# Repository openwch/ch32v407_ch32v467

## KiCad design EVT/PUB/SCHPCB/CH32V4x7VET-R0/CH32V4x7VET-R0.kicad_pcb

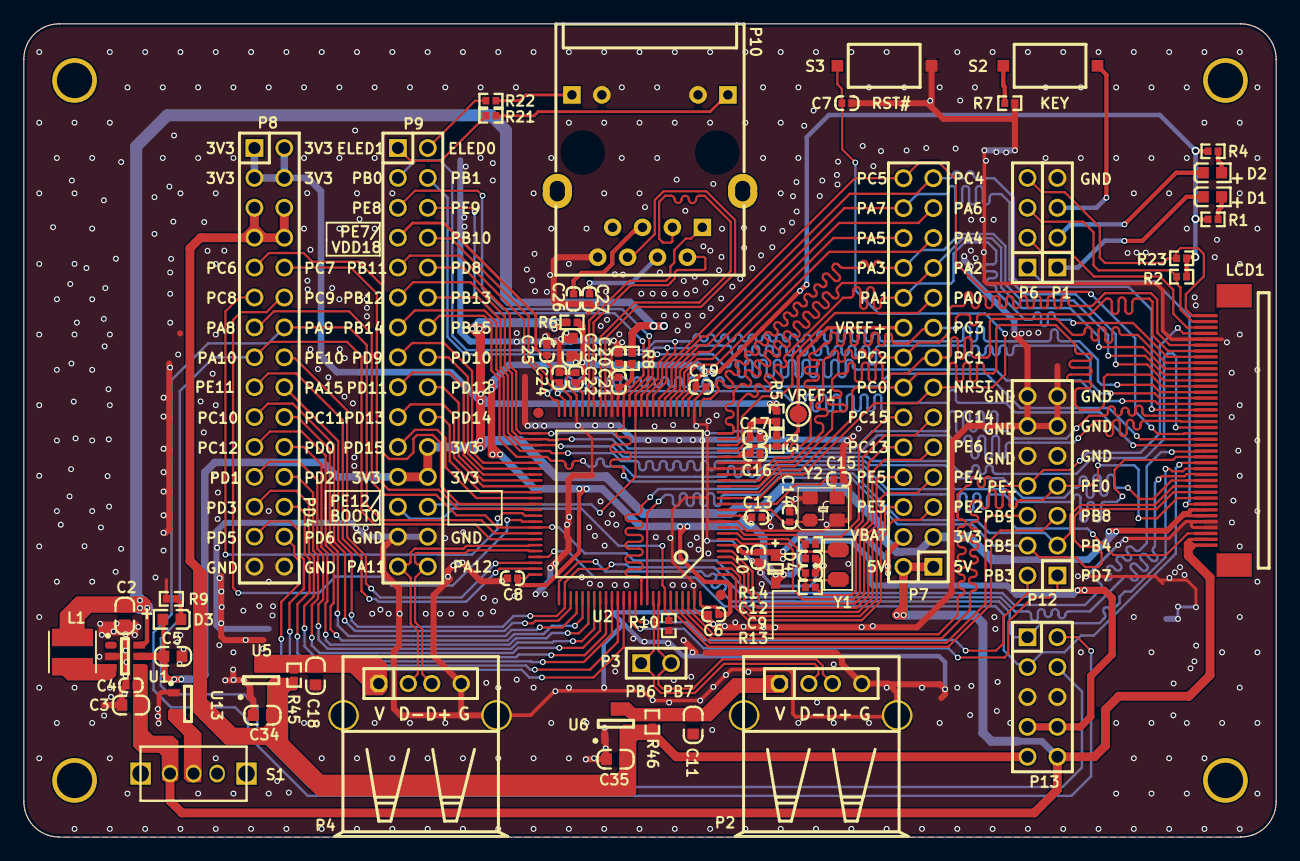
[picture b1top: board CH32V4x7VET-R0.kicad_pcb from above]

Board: 2 copper layers, 106.4 x 69.1 mm, 73 parts (0 on the bottom side), 117 nets.

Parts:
C2: NC(10uF); 0603_C
C3, C5, C11, C18, C23, C34, C35: 10uF; 0603_C
C4: 1uF; 0402_C
C6, C8, C10, C13, C16, C17, C19, C21, C22, C24, C26, C27: 0.1uF; 0402_C
C7: 22nF; 0402_C
C9, C12: 12pF; 0402_C
C14, C15: 18pF; 0402_C
C20, C25: 2.2uF; 0402_C
D1: BLUE; 0603+
D2, D3: RED; 0603+
D4: B0520WS; SOD-323
L1: NC(2.2uH); CD32
LCD1: NC(MY-RGB); FPC40P-0.5-FK750M3
P1: HEADER 4; SIP4-2.54mm
P2: USBHS2; USBAF
P3: HEADER 2; SIP2-2.54mm
P4: USBHS1; USBAF
P6: NC(HEADER 4); SIP4-2.54mm
P7: HEADER 14x2; IDC28-2.54MM
P8, P9: HEADER 15x2; IDC30-2.54MM
P10: HR911105A
P12: HEADER 7x2; IDC14-2.54mm
P13: LINK; IDC10-2.54mm
R1, R4, R9: 1K; 0402
R2, R23: NC(4.7K); 0402
R3, R5, R6: 0R; 0402
R7, R10: 10K; 0402
R8, R13, R14: NC(0R); 0402
R21, R22: 470; 0402
R45, R46: NC(0Ω); 0402
S1: SW SPDT; SW1
S2: KEY; SMD_6.1x3.65x2.5mm-KEY
S3: RST#; SMD_6.1x3.65x2.5mm-KEY
U1: CH2003V; SOT-23-6
U2: CH32V467VET; LQFP100
U5, U6, U13: CH213; SOT-23-3
VREF1: PAD; TESTPOINT1
Y1: 32768Hz; FC-135
Y2: 25MHz; XT3225

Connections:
1V2: C2.2, L1.2, R8.2, U1.6
3V3: C5.2, D3.1, LCD1.6, LCD1.7, P7.3, P8.1, P8.2, P8.3, P8.4, P9.22, P9.23, P9.24, R5.1, R6.1, U1.5
+5V: C3.2, C4.2, LCD1.1, LCD1.2, P7.1, P7.2, P13.10, S1.2, U1.4
BOOT0: P9.25, R10.2, U2.94
BOOT1: LCD1.25, P9.26, U2.37
ELED0: P9.2, R22.1
ELED1: P9.1, R21.1
GND: C2.1, C3.1, C4.1, C5.1, C6.1, C7.1, C8.2, C9.1, C10.1, C11.2, C12.1, C13.2, C14.1, C15.1, C16.2, C17.2, C18.2, C19.1, C20.1, C21.1, C22.1, C23.1, C24.1, C25.1, C26.1, C27.1, C34.2, C35.2, LCD1.4, LCD1.5, LCD1.36, P1.4, P2.0, P2.4, P4.0, P4.4, P8.29, P8.30, P9.27, P9.28, P10.8, P10.10, P10.11, P12.9, P12.10, P12.11, P12.12, P12.13, P12.14, P13.5, P13.6, R7.1, R9.2, R10.1, S3.1, U1.2, U2.10, U2.19, U2.20, U2.27, U2.41, U2.47, U2.99, U5.1, U6.1, U13.1, Y2.2, Y2.4
KEY: P1.3, S2.1
LED1: D1.2, P1.1
LED2: D2.2, P1.2
MDIRN: P10.6, U2.42
MDIRP: P10.3, U2.43
MDITN: P10.2, U2.44
MDITP: P10.1, U2.45
NRST: C7.2, P7.13, S3.2, U2.14
NetC26_2: C26.2, P10.5
NetC27_2: C27.2, P10.4
NetD1_1: D1.1, R1.2
NetD2_1: D2.1, R4.2
NetD3_2: D3.2, R9.1
NetL1_1: L1.1, U1.3
NetP10_9: P10.9, R21.2
NetP10_12: P10.12, R22.2
NetR7_2: R7.2, S2.2
NetS1_1: S1.1, U13.2
PA0: P7.19, U2.23
PA1: LCD1.33, P7.20, U2.24
PA2: LCD1.31, P7.21, U2.25
PA3: LCD1.30, P7.22, U2.26
PA4: P7.23, U2.29
PA5: P7.24, U2.30
PA6: P7.25, U2.31
PA7: LCD1.29, P7.26, U2.32
PA8: LCD1.17, P8.13, U2.67
PA9: P8.14, P13.2, U2.68
PA10: P8.15, P13.4, U2.69
PA11: P4.2, P9.29, U2.70
PA12: P4.3, P9.30, U2.71
PA13: LCD1.15, P13.3, U2.72
PA14: LCD1.14, P13.1, U2.76
PA15: LCD1.13, P8.18, U2.77
PB0: LCD1.27, P9.3, U2.35
PB1: LCD1.26, P9.4, U2.36
PB3: P12.2, U2.89
PB4: LCD1.11, P12.3, U2.90
PB5: LCD1.10, P12.4, U2.91
PB6: P2.2, P3.1, U2.92
PB7: P2.3, P3.2, U2.93
PB8: P12.5, U2.95
PB9: P12.6, U2.96
PB10: LCD1.18, P9.8, U2.49
PB11: LCD1.19, P9.9, U2.50
PB12: LCD1.22, P9.11, U2.52
PB13: LCD1.21, P9.12, U2.53
PB14: LCD1.12, P9.13, U2.54
PB15: LCD1.16, P9.14, U2.55
PC0: LCD1.28, P7.14, U2.15
PC1: LCD1.32, P7.15, U2.16
PC2: LCD1.35, P7.16, U2.17
PC3: LCD1.34, P7.17, U2.18
PC4: LCD1.24, P7.27, U2.33
PC5: LCD1.20, P7.28, U2.34
PC6: P8.9, U2.63
PC7: P8.10, U2.64
PC8: P8.11, U2.65
PC9: P8.12, U2.66
PC10: P8.19, U2.78
PC11: P8.20, U2.79
PC12: P8.21, U2.80
PC13: P7.10, U2.7
PC14: P7.11, R13.1
PC15: P7.12, R14.1
PD0: P8.22, U2.81
PD1: P8.23, U2.82
PD2: P8.24, U2.83
PD3: P8.25, U2.84
PD4: P8.26, U2.85
PD5: P8.27, U2.86
PD6: P8.28, U2.87
PD7: P12.1, U2.88
PD8: LCD1.23, P9.10, U2.51
PD9: P9.15, U2.56
PD10: P9.16, U2.57
PD11: P9.17, U2.58
PD12: P9.18, U2.59
PD13: P9.19, U2.60
PD14: P9.20, U2.61
PD15: P9.21, U2.62
PE0: LCD1.9, P12.7, U2.97
PE1: LCD1.37, P12.8, U2.98
PE2: P7.5, U2.1
PE3: P7.6, U2.2
PE4: P7.7, U2.3
PE5: P7.8, U2.4
PE6: P7.9, U2.5
PE8: P9.5, U2.38
PE9: LCD1.3, P9.6, U2.39
PE10: P8.16, U2.73
PE11: P8.17, U2.74
TOUCH_INT: LCD1.38, P6.2
TOUCH_RST: LCD1.8, P6.1
TOUCH_SCLK: LCD1.39, P6.3, R2.2
TOUCH_SDA: LCD1.40, P6.4, R23.2
VBAT: C10.2, D4.1, P7.4, U2.6
VBUS: C34.1, C35.1, P8.5, P8.6, P8.7, P8.8, P13.9, R45.1, R46.1, U5.2, U6.2, U13.3
VBUS_P1: C18.1, P4.1, R45.2, U5.3
VBUS_P2: C11.1, P2.1, R46.2, U6.3
VDD: C6.2, C8.1, C13.1, C19.2, C22.2, C23.2, D4.2, P13.7, P13.8, R1.1, R2.1, R4.1, R6.2, R23.1, U2.11, U2.28, U2.46, U2.75, U2.100
VDD18: C24.2, C25.2, P9.7, U2.48
VDDA: C17.1, R3.1, R5.2, U2.22
VDDK: C20.2, C21.2, R8.1, U2.40
VREF+: C16.1, P7.18, R3.2, U2.21, VREF1.1
X32KI: C9.2, R13.2, U2.8, Y1.1
X32KO: C12.2, R14.2, U2.9, Y1.2
XI: C14.2, U2.12, Y2.1
XO: C15.2, U2.13, Y2.3

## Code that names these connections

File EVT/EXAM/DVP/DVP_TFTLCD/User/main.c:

/********************************** (C) COPYRIGHT *******************************
* File Name          : main.c
* Author             : WCH
* Version            : V1.0.1
* Date               : 2026/10/14
* Description        : Main program body.
*********************************************************************************
* Copyright (c) 2021 Nanjing Qinheng Microelectronics Co., Ltd.
* Attention: This software (modified or not) and binary are used for 
* microcontroller manufactured by Nanjing Qinheng Microelectronics.
*******************************************************************************/
#include "debug.h"
#include "lcd.h"
#include "ov5640.h"
#include "ov2640.h"
/*
 *@Note
  DVP routine to operate ov2640\ov5640 camera video mode to display image on TFTLCD:
  DVP--PIN:
    D10--PD6
    D11--PD2
    D8--PC10
    D9--PC12
    DPWDN--PE5
    DPCLK--PA6
    D7--PB9
    D6--PB8
    D5--PB6
    D4--PC11
    D3--PC9
    D2--PC8
    D1--PA10
    D0--PA9
    RESET--PE4
    SCL--PE2
    SDA--PE3
    HSYNC--PA4
    VSYNC--PA5
  FSMC routine to operate TFTLCD-LCD--PIN:
    PD7--NE1(CS)
    PD12--RS
    PD5 --FSMC_NEW(WR)
    PD4 --FSMC_NOE(RD)
    PA15 --LCDRST#
    PD14--FSMC_D0
    PD15--FSMC_D1
    PD0 --FSMC_D2
    PD1--FSMC_D3
    PE7--FSMC_D4
    PE8 --FSMC_D5
    PE9 --FSMC_D6
    PE10--FSMC_D7
    PE11--FSMC_D8
    PB11--FSMC_D9
    PB12--FSMC_D10
    PB13--FSMC_D11
    PB14--FSMC_D12
    PD8 --FSMC_D13
    PD9 --FSMC_D14
    PD10--FSMC_D15
    PB1--BL
 */

/* Camera module selection */
#define OV2640_Module  0
#define OV5640_Module  1
#define CAMERA_SELECT  OV5640_Module

#if(CAMERA_SELECT == OV2640_Module)
uint16_t ImageDataOv2640[2 * OV2640_RGB565_WIDTH] = {0};
#elif(CAMERA_SELECT == OV5640_Module)
uint16_t ImageDataOv5640[2 * OV5640_RGB565_WIDTH] = {0};
#endif

volatile UINT32 frame_cnt = 0;
volatile UINT32 href_cnt = 0;

void DVP_IRQHandler(void) __attribute__ ((interrupt ("WCH-Interrupt-fast")));

/*********************************************************************
 * @fn      DMA_SRAMLCD_Enable
 *
 * @brief   Enable SRAMLCD DMA transmission
 *
 * @return  none
 */
void DMA_SRAMLCD_Enable(void)
{
    DMA_Cmd(DMA2_Channel5, DISABLE );
    DMA_SetCurrDataCounter(DMA2_Channel5,lcddev.width);
    DMA_Cmd(DMA2_Channel5, ENABLE);
}

/*********************************************************************
 * @fn      LCD_Reset_GPIO_Init
 *
 * @brief   Init LCD reset GPIO.
 *
 * @return  none
 */
void LCD_Reset_GPIO_Init(void)
{
    GPIO_InitTypeDef  GPIO_InitStructure={0};

    RCC_PB2PeriphClockCmd(RCC_PB2Periph_GPIOA, ENABLE);

    GPIO_InitStructure.GPIO_Pin = GPIO_Pin_15;
    GPIO_InitStructure.GPIO_Mode = GPIO_Mode_Out_PP;
    GPIO_InitStructure.GPIO_Speed = GPIO_Speed_High;
    GPIO_Init(GPIOA, &GPIO_InitStructure);
    GPIO_SetBits(GPIOA,GPIO_Pin_15);
}

/*********************************************************************
 * @fn      DMA_SRAMLCD_Init
 *
 * @brief   Init SRAMLCD DMA
 *
 * @param   ddr: DVP data memory base addr.
 *
 * @return  none
 */
void DMA_SRAMLCD_Init(u32 ddr)
{
    DMA_InitTypeDef DMA_InitStructure={0};

    RCC_HBPeriphClockCmd(RCC_HBPeriph_DMA2, ENABLE);

    DMA_DeInit(DMA2_Channel5);

    DMA_InitStructure.DMA_PeripheralBaseAddr = ddr;
    DMA_InitStructure.DMA_MemoryBaseAddr = (u32)&LCD->LCD_RAM;
    DMA_InitStructure.DMA_DIR = DMA_DIR_PeripheralSRC;
    DMA_InitStructure.DMA_BufferSize = 0;
    DMA_InitStructure.DMA_PeripheralInc = DMA_PeripheralInc_Enable;
    DMA_InitStructure.DMA_MemoryInc = DMA_MemoryInc_Disable;
    DMA_InitStructure.DMA_PeripheralDataSize = DMA_PeripheralDataSize_HalfWord;
    DMA_InitStructure.DMA_MemoryDataSize = DMA_MemoryDataSize_HalfWord;
    DMA_InitStructure.DMA_Mode = DMA_Mode_Normal;
    DMA_InitStructure.DMA_Priority = DMA_Priority_Medium;
    DMA_InitStructure.DMA_M2M = DMA_M2M_Enable;
    DMA_Init(DMA2_Channel5, &DMA_InitStructure);
}

/*********************************************************************
 * @fn      DVP_Function_Init
 *
 * @brief   Init DVP
 *
 * @return  none
 */
void DVP_Function_Init(void) 
{
    DVP_InitTypeDef DVP_InitStructure = {0};
    RCC_HBPeriphClockCmd(RCC_HBPeriph_DVP, ENABLE);

    DVP_DeInit();
    DVP_InitStructure.DVP_DataSize = DVP_DataSize_8b;
#if(CAMERA_SELECT == OV2640_Module)
    DVP_InitStructure.DVP_COL_NUM = OV2640_RGB565_WIDTH * 2;
    DVP_InitStructure.DVP_ROW_NUM = OV2640_RGB565_HEIGHT;
#elif(CAMERA_SELECT == OV5640_Module)
    DVP_InitStructure.DVP_COL_NUM = OV5640_RGB565_WIDTH * 2;
    DVP_InitStructure.DVP_ROW_NUM = OV5640_RGB565_HEIGHT;
#endif
    DVP_InitStructure.DVP_HCLK_P = DVP_Hclk_P_Rising;
    DVP_InitStructure.DVP_HSYNC_P = DVP_Hsync_P_High;
    DVP_InitStructure.DVP_VSYNC_P = DVP_Vsync_P_High;
#if(CAMERA_SELECT == OV2640_Module)
    DVP_InitStructure.DVP_DMA_BUF0_Addr = (uint32_t)(ImageDataOv2640);
    DVP_InitStructure.DVP_DMA_BUF1_Addr = (uint32_t)(ImageDataOv2640 + OV2640_RGB565_WIDTH);
#elif(CAMERA_SELECT == OV5640_Module)
    DVP_InitStructure.DVP_DMA_BUF0_Addr = (uint32_t)(ImageDataOv5640);
    DVP_InitStructure.DVP_DMA_BUF1_Addr = (uint32_t)(ImageDataOv5640 + OV5640_RGB565_WIDTH);
#endif
    DVP_InitStructure.DVP_FrameCapRate = DVP_FrameCapRate_100P;
    DVP_InitStructure.DVP_JPEGMode = DISABLE;
    DVP_InitStructure.DVP_CaptureMode = DVP_CaptureMode_Continuous;
    DVP_Init(&DVP_InitStructure);

    DVP_ReceiveCircuitResetCmd(DISABLE);
    DVP_FIFO_ResetCmd(DISABLE);

    NVIC_EnableIRQ(DVP_IRQn);
    NVIC_SetPriority(DVP_IRQn, 0);

    DVP_ITConfig(DVP_IT_STR_FRM | DVP_IT_ROW_DONE | DVP_IT_FRM_DONE | DVP_IT_FIFO_OV | DVP_IT_STP_FRM, ENABLE);

    DVP_DMACmd(ENABLE);
    DVP_Cmd(ENABLE);
}

/*********************************************************************
 * @fn      DVP_IRQHandler
 *
 * @brief   This function handles DVP exception.
 *
 * @return  none
 */
void DVP_IRQHandler(void)
{
    if(DVP_GetITStatus(DVP_IT_ROW_DONE) != RESET)
    {
        DVP_ClearITPendingBit(DVP_IT_ROW_DONE);

        if(href_cnt % 2)
        {
            /* Send DVP data to LCD */
            DMA_Cmd(DMA2_Channel5, DISABLE);    
#if(CAMERA_SELECT == OV2640_Module)
            DMA_SetCurrDataCounter(DMA2_Channel5, OV2640_RGB565_WIDTH * 2);
            DMA2_Channel5->PADDR = (uint32_t)(ImageDataOv2640);
#elif(CAMERA_SELECT == OV5640_Module)
            DMA_SetCurrDataCounter(DMA2_Channel5, OV5640_RGB565_WIDTH * 2);
            DMA2_Channel5->PADDR = (uint32_t)(ImageDataOv5640);
#endif     
            DMA_Cmd(DMA2_Channel5, ENABLE);
        }
        href_cnt++;
    }

    if(DVP_GetITStatus(DVP_IT_FRM_DONE) != RESET)
    {
        DVP_ClearITPendingBit(DVP_IT_FRM_DONE);
        href_cnt = 0;
    }

    if(DVP_GetITStatus(DVP_IT_STR_FRM) != RESET)
    {
        DVP_ClearITPendingBit(DVP_IT_STR_FRM);
        frame_cnt++;
    }

    if(DVP_GetITStatus(DVP_IT_STP_FRM) != RESET)
    {
        DVP_ClearITPendingBit(DVP_IT_STP_FRM);
    }

    if(DVP_GetITStatus(DVP_IT_FIFO_OV) != RESET)
    {
        DVP_ClearITPendingBit(DVP_IT_FIFO_OV);
    }
}

/*********************************************************************
 * @fn      main
 *
 * @brief   Main program.
 *
 * @return  none
 */
int main(void)
{
	SystemCoreClockUpdate();
	Delay_Init();
	USART_Printf_Init(115200);	
	printf("SystemClk:%u\r\n",SystemCoreClock);
	printf( "ChipID:%08x\r\n", DBGMCU_GetCHIPID() );

#if(CAMERA_SELECT == OV2640_Module)
    LCD_Reset_GPIO_Init();
    LCD_Init();   
   while(OV2640_Init())
    {
        printf("Camera Initialize failed.\r\n");
        Delay_Ms(1000);
    }
    printf("Camera Initialize Success.\r\n");

    Delay_Ms(1000);

    OV2640_RGB565_Mode_Init();
    Delay_Ms(1000);   

    printf("RGB565 Mode...\r\n");

    DMA_SRAMLCD_Init((u32)ImageDataOv2640);
    DVP_Function_Init();
#endif

#if(CAMERA_SELECT == OV5640_Module)
    uint8_t tempstr[50]; 
    LCD_Reset_GPIO_Init();
    LCD_Init();   
    LCD_Display_Dir(1);
    
    sprintf ((char*)tempstr,"height: %d  width: %d  id: %#x\n", lcddev.height, lcddev.width, lcddev.id);
    LCD_ShowString(0,120-12,320,48,16,tempstr);

    LCD_SetCursor (0, 0);
    LCD_WriteRAM_Prepare();

    while(OV5640_Init()) {
        printf("Camera Initialize failed.\r\n");
        Delay_Ms(1000);
    }
    printf("Camera Initialize Success.\r\n");

    OV5640_RGB565_Mode_Init();
    Delay_Ms(500);
    printf("RGB565 Mode...\r\n");
    DMA_SRAMLCD_Init((uint32_t)ImageDataOv5640);
    DVP_Function_Init();
#endif

    while(1);
}

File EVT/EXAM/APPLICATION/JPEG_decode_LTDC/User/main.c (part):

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    RCC_PB2PeriphClockCmd(RCC_PB2Periph_GPIOE, ENABLE);
    GPIO_PinRemapConfig(GPIO_Remap_SWJ_Disable, ENABLE);

    // LTDC_CLK PE1
    GPIO_InitStructure.GPIO_Pin   = GPIO_Pin_1;
    GPIO_InitStructure.GPIO_Speed = GPIO_Speed_High;
    GPIO_InitStructure.GPIO_Mode  = GPIO_Mode_AF_PP;
    GPIO_Init(GPIOE, &GPIO_InitStructure);

    // LTDC_HSYNC PB4
    GPIO_InitStructure.GPIO_Pin   = GPIO_Pin_4;
    GPIO_InitStructure.GPIO_Speed = GPIO_Speed_High;
    GPIO_InitStructure.GPIO_Mode  = GPIO_Mode_AF_PP;
    GPIO_Init(GPIOB, &GPIO_InitStructure);

    // LTDC_VSYNC PB5
    GPIO_InitStructure.GPIO_Pin   = GPIO_Pin_5;
    GPIO_InitStructure.GPIO_Speed = GPIO_Speed_High;
    GPIO_InitStructure.GPIO_Mode  = GPIO_Mode_AF_PP;
    GPIO_Init(GPIOB, &GPIO_InitStructure);

    // LTDC_DE PE0
    GPIO_InitStructure.GPIO_Pin   = GPIO_Pin_0;
    GPIO_InitStructure.GPIO_Speed = GPIO_Speed_High;
    GPIO_InitStructure.GPIO_Mode  = GPIO_Mode_AF_PP;
    GPIO_Init(GPIOE, &GPIO_InitStructure);

    // LTDC_R0 PC0
    GPIO_InitStructure.GPIO_Pin   = GPIO_Pin_0;
    GPIO_InitStructure.GPIO_Speed = GPIO_Speed_High;
    GPIO_InitStructure.GPIO_Mode  = GPIO_Mode_AF_PP;
    GPIO_Init(GPIOC, &GPIO_InitStructure);

    // LTDC_R1 PC1
    GPIO_InitStructure.GPIO_Pin   = GPIO_Pin_1;
    GPIO_InitStructure.GPIO_Speed = GPIO_Speed_High;
    GPIO_InitStructure.GPIO_Mode  = GPIO_Mode_AF_PP;
    GPIO_Init(GPIOC, &GPIO_InitStructure);

    // LTDC_R2 PC2
    GPIO_InitStructure.GPIO_Pin   = GPIO_Pin_2;
    GPIO_InitStructure.GPIO_Speed = GPIO_Speed_High;
    GPIO_InitStructure.GPIO_Mode  = GPIO_Mode_AF_PP;
    GPIO_Init(GPIOC, &GPIO_InitStructure);

    // LTDC_R3 PC3
    GPIO_InitStructure.GPIO_Pin   = GPIO_Pin_3;
    GPIO_InitStructure.GPIO_Speed = GPIO_Speed_High;
    GPIO_InitStructure.GPIO_Mode  = GPIO_Mode_AF_PP;
    GPIO_Init(GPIOC, &GPIO_InitStructure);

    // LTDC_R4 PA1
    GPIO_InitStructure.GPIO_Pin   = GPIO_Pin_1;
    GPIO_InitStructure.GPIO_Speed = GPIO_Speed_High;
    GPIO_InitStructure.GPIO_Mode  = GPIO_Mode_AF_PP;
    GPIO_Init(GPIOA, &GPIO_InitStructure);

    // LTDC_R5 PA2
    GPIO_InitStructure.GPIO_Pin   = GPIO_Pin_2;
    GPIO_InitStructure.GPIO_Speed = GPIO_Speed_High;
    GPIO_InitStructure.GPIO_Mode  = GPIO_Mode_AF_PP;
    GPIO_Init(GPIOA, &GPIO_InitStructure);

    // LTDC_R6 PA3
    GPIO_InitStructure.GPIO_Pin   = GPIO_Pin_3;
    GPIO_InitStructure.GPIO_Speed = GPIO_Speed_High;
    GPIO_InitStructure.GPIO_Mode  = GPIO_Mode_AF_PP;
    GPIO_Init(GPIOA, &GPIO_InitStructure);

    // LTDC_R7 PA7
    GPIO_InitStructure.GPIO_Pin   = GPIO_Pin_7;
    GPIO_InitStructure.GPIO_Speed = GPIO_Speed_High;
    GPIO_InitStructure.GPIO_Mode  = GPIO_Mode_AF_PP;
    GPIO_Init(GPIOA, &GPIO_InitStructure);

    // LTDC_G0 PC4
    GPIO_InitStructure.GPIO_Pin   = GPIO_Pin_4;
    GPIO_InitStructure.GPIO_Speed = GPIO_Speed_High;
    GPIO_InitStructure.GPIO_Mode  = GPIO_Mode_AF_PP;
    GPIO_Init(GPIOC, &GPIO_InitStructure);

    // LTDC_G1 PC5
    GPIO_InitStructure.GPIO_Pin   = GPIO_Pin_5;
    GPIO_InitStructure.GPIO_Speed = GPIO_Speed_High;
    GPIO_InitStructure.GPIO_Mode  = GPIO_Mode_AF_PP;
    GPIO_Init(GPIOC, &GPIO_InitStructure);

    // LTDC_G2 PB0
    GPIO_InitStructure.GPIO_Pin   = GPIO_Pin_0;
    GPIO_InitStructure.GPIO_Speed = GPIO_Speed_High;
    GPIO_InitStructure.GPIO_Mode  = GPIO_Mode_AF_PP;
    GPIO_Init(GPIOB, &GPIO_InitStructure);

    // LTDC_G3 PB1
    GPIO_InitStructure.GPIO_Pin   = GPIO_Pin_1;
    GPIO_InitStructure.GPIO_Speed = GPIO_Speed_High;
    GPIO_InitStructure.GPIO_Mode  = GPIO_Mode_AF_PP;
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    GPIO_InitStructure.GPIO_Mode  = GPIO_Mode_AF_PP;
    GPIO_Init(GPIOB, &GPIO_InitStructure);

    // LTDC_G5 PD8
    GPIO_InitStructure.GPIO_Pin   = GPIO_Pin_8;
    GPIO_InitStructure.GPIO_Speed = GPIO_Speed_High;
    GPIO_InitStructure.GPIO_Mode  = GPIO_Mode_AF_PP;
    GPIO_Init(GPIOD, &GPIO_InitStructure);

    // LTDC_G6 PB12
    GPIO_InitStructure.GPIO_Pin   = GPIO_Pin_12;
    GPIO_InitStructure.GPIO_Speed = GPIO_Speed_High;
    GPIO_InitStructure.GPIO_Mode  = GPIO_Mode_AF_PP;
    GPIO_Init(GPIOB, &GPIO_InitStructure);

    // LTDC_G7 PB13
    GPIO_InitStructure.GPIO_Pin   = GPIO_Pin_13;
    GPIO_InitStructure.GPIO_Speed = GPIO_Speed_High;
    GPIO_InitStructure.GPIO_Mode  = GPIO_Mode_AF_PP;
    GPIO_Init(GPIOB, &GPIO_InitStructure);

    // LTDC_B0 PB14
    GPIO_InitStructure.GPIO_Pin   = GPIO_Pin_14;
    GPIO_InitStructure.GPIO_Speed = GPIO_Speed_High;
    GPIO_InitStructure.GPIO_Mode  = GPIO_Mode_AF_PP;
    GPIO_Init(GPIOB, &GPIO_InitStructure);

    // LTDC_B1 PB15
    GPIO_InitStructure.GPIO_Pin   = GPIO_Pin_15;
    GPIO_InitStructure.GPIO_Speed = GPIO_Speed_High;
    GPIO_InitStructure.GPIO_Mode  = GPIO_Mode_AF_PP;
    GPIO_Init(GPIOB, &GPIO_InitStructure);

    // LTDC_B2 PB11
    GPIO_InitStructure.GPIO_Pin   = GPIO_Pin_11;
    GPIO_InitStructure.GPIO_Speed = GPIO_Speed_High;
    GPIO_InitStructure.GPIO_Mode  = GPIO_Mode_AF_PP;
    GPIO_Init(GPIOB, &GPIO_InitStructure);

    // LTDC_B3 PB10
    GPIO_InitStructure.GPIO_Pin   = GPIO_Pin_10;
    GPIO_InitStructure.GPIO_Speed = GPIO_Speed_High;
    GPIO_InitStructure.GPIO_Mode  = GPIO_Mode_AF_PP;
    GPIO_Init(GPIOB, &GPIO_InitStructure);

    // LTDC_B4 PA8
    GPIO_InitStructure.GPIO_Pin   = GPIO_Pin_8;
    GPIO_InitStructure.GPIO_Speed = GPIO_Speed_High;
    GPIO_InitStructure.GPIO_Mode  = GPIO_Mode_AF_PP;
    GPIO_Init(GPIOA, &GPIO_InitStructure);

    // LTDC_B5 PA13
    GPIO_InitStructure.GPIO_Pin   = GPIO_Pin_13;
    GPIO_InitStructure.GPIO_Speed = GPIO_Speed_High;
    GPIO_InitStructure.GPIO_Mode  = GPIO_Mode_AF_PP;
    GPIO_Init(GPIOA, &GPIO_InitStructure);

    // LTDC_B6 PA14
    GPIO_InitStructure.GPIO_Pin   = GPIO_Pin_14;
    GPIO_InitStructure.GPIO_Speed = GPIO_Speed_High;
    GPIO_InitStructure.GPIO_Mode  = GPIO_Mode_AF_PP;
    GPIO_Init(GPIOA, &GPIO_InitStructure);

    // LTDC_B7 PA15
    GPIO_InitStructure.GPIO_Pin   = GPIO_Pin_15;
    GPIO_InitStructure.GPIO_Speed = GPIO_Speed_High;
    GPIO_InitStructure.GPIO_Mode  = GPIO_Mode_AF_PP;
    GPIO_Init(GPIOA, &GPIO_InitStructure);

    // 背光灯使能 PE9
    GPIO_InitStructure.GPIO_Pin   = GPIO_Pin_9;
    GPIO_InitStructure.GPIO_Speed = GPIO_Speed_High;
    GPIO_InitStructure.GPIO_Mode  = GPIO_Mode_Out_PP;
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
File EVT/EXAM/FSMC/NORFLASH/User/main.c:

/********************************** (C) COPYRIGHT *******************************
* File Name          : main.c
* Author             : WCH
* Version            : V1.0.0
* Date               : 2026/10/14
* Description        : Main program body.
*********************************************************************************
* Copyright (c) 2024 Nanjing Qinheng Microelectronics Co., Ltd.
* Attention: This software (modified or not) and binary are used for 
* microcontroller manufactured by Nanjing Qinheng Microelectronics.
*******************************************************************************/

/*
 *@Note
   This example is used to demonstrate the FSMC interface operating NorFlash-MT28EW128ABA1LJS-0SIT.
  PIN:
    FSMC_NADV     -    PB7
    FSMC_NOE      -    PD4  (OE)
    FSMC_NWE      -    PD5  (WE)
    FSMC_NWAIT    -    PD6  (RY/BY#)
    FSMC_NE1      -    PD7  (CE)
    FSMC_D/A0     -    PD14
    FSMC_D/A1     -    PD15
    FSMC_D/A2     -    PD0
    FSMC_D/A3     -    PD1
    FSMC_D/A4     -    PE7
    FSMC_D/A5     -    PE8
    FSMC_D/A6     -    PE9
    FSMC_D/A7     -    PE10
    FSMC_D/A8     -    PE11
    FSMC_D/A9     -    PB11
    FSMC_D/A10    -    PB12
    FSMC_D/A11    -    PB13
    FSMC_D/A12    -    PB14
    FSMC_D/A13    -    PD8
    FSMC_D/A14    -    PD9
    FSMC_D/A15    -    PD10
    FSMC_A16      -    PD11
    FSMC_A17      -    PD12
    FSMC_A18      -    PD13
    FSMC_A19      -    PE3
    FSMC_A20      -    PE4
    FSMC_A21      -    PE5
    FSMC_A22      -    PE6

  The address line and data line of this routine are multiplexed
  and need to use a latch.
*/

#include "debug.h"
#include "FSMC_NOR.h"
/* Global define */

/* Global Variable */
uint16_t TxBuffer[BUFFER_SIZE];
uint16_t RxBuffer[BUFFER_SIZE];
uint32_t WriteReadStatus = 0, Index = 0;
NOR_IDTypeDef NOR_ID;


/*********************************************************************
 * @fn      main
 *
 * @brief   Main program.
 *
 * @return  none
 */
int main(void)
{

    SystemCoreClockUpdate();
    Delay_Init();
    USART_Printf_Init(115200);	
    printf ("SystemCoreClk:%lu\r\n", (unsigned long)SystemCoreClock);
    printf( "ChipID:%08x\r\n", DBGMCU_GetCHIPID() );

    printf("PSRAM TEST\r\n");
    FSMC_NorFlash_Init();
    NOR_ReadID(&NOR_ID);
    NOR_ReturnToReadMode();
    NOR_EraseBlock(WRITE_READ_ADDR);
    Fill_Buffer(TxBuffer, BUFFER_SIZE, 0x01);
    NOR_WriteBuffer(TxBuffer, WRITE_READ_ADDR, BUFFER_SIZE);
    NOR_ReadBuffer(RxBuffer, WRITE_READ_ADDR, BUFFER_SIZE);
    for (Index = 0x00; (Index < BUFFER_SIZE) && (WriteReadStatus == 0); Index++)
    {
        if (RxBuffer[Index] != TxBuffer[Index])
        {
            WriteReadStatus = Index + 1;
            printf("RxBuffer[%d]=%x\r\n",Index,RxBuffer[Index]);
            printf("TxBuffer[%d]=%x\r\n",Index,TxBuffer[Index]);
        }
    }
    if (WriteReadStatus == 0)
    {
        /* OK */
        printf("sucess\r\n");
    }
    else
    {
        /* KO */
        printf("error\r\n");
    }
    while(1);
}

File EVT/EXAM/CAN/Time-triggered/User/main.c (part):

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 *of TTCAN in the application manual.
 *
 *Current bitrate is 833333.33Hz. If you want to change the bit rate to config the bitrate to 250k,
 *change the PB1 clock to 48M.If you want to configure it yourself, please refer to our manual.
 */

#include "debug.h"
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
/**
 * @brief  CAN Tx pin table
 * @note   CAN1: PA12, PB9, PD1
 */
const CANPinTable_t CANTXPinTable[] = {
    {CAN1, GPIOA, 12, 0}, {CAN1, GPIOB, 9, GPIO_Remap1_CAN1}, {CAN1, GPIOD, 1, GPIO_Remap2_CAN1},
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
/**
 * @brief  CAN Rx pin table
 * @note   CAN1: PA11, PB8, PD0
 */
const CANPinTable_t CANRXPinTable[] = {
    {CAN1, GPIOA, 11, 0}, {CAN1, GPIOB, 8, GPIO_Remap1_CAN1}, {CAN1, GPIOD, 0, GPIO_Remap2_CAN1},
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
